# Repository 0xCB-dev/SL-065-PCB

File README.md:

# Synth Labs 065 PCB
## 65% Keyboard

Licence | OSHWA
:-------------------------:|:-------------------------:
 | TBD

### PCB:
KiCad version 6 stable

Top | Bottom
:-------------------------:|:-------------------------:
  |  

#### BOM:

[ibom pcb](https://files.0xcb.dev/0xCB/SL-065-PCB/pcb.html)

##### Hotswap PCB

| References                             | Value        | Footprint                                       | Quantity | Mouser                                                                                                              |
|----------------------------------------|--------------|-------------------------------------------------|----------|---------------------------------------------------------------------------------------------------------------------|

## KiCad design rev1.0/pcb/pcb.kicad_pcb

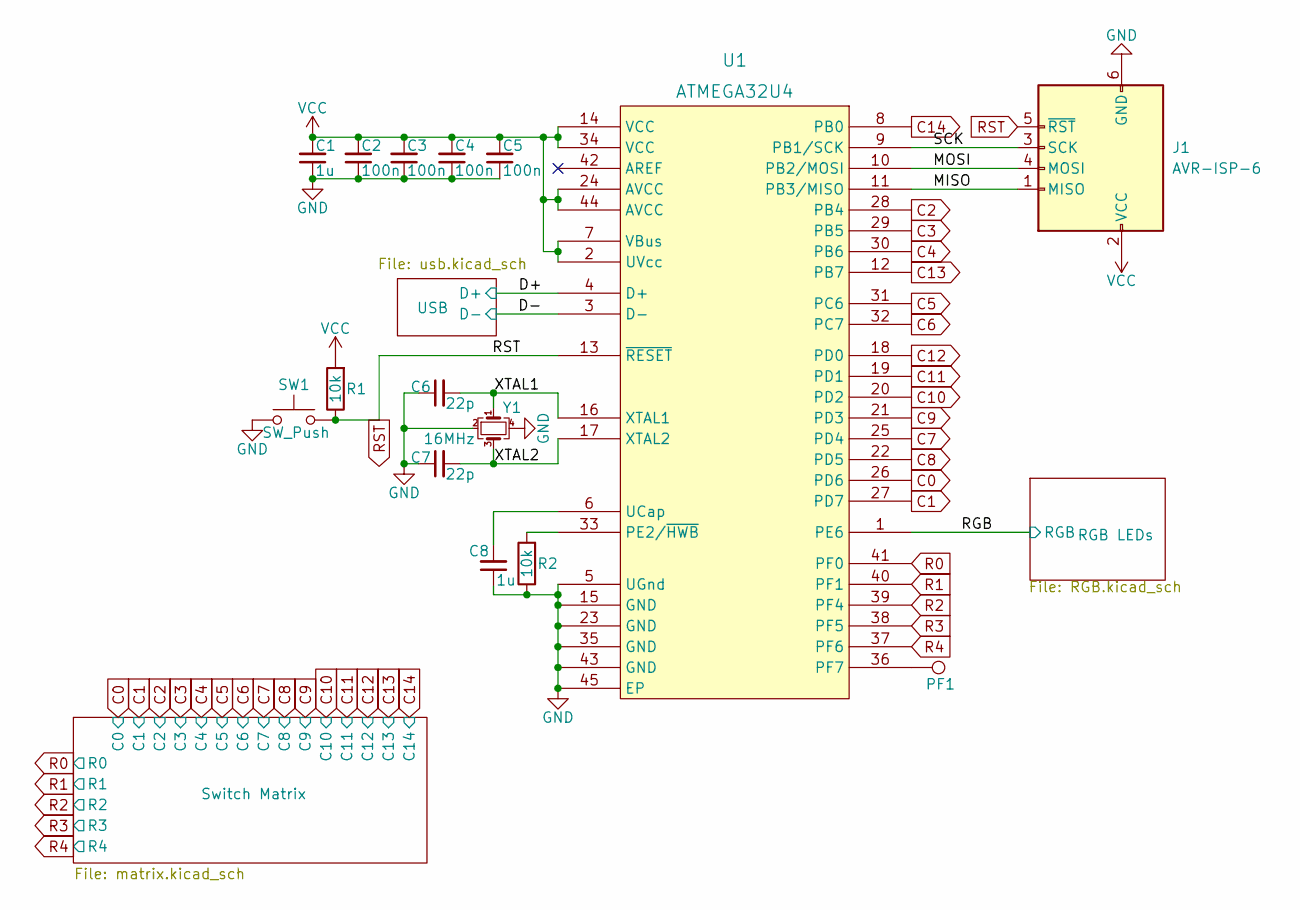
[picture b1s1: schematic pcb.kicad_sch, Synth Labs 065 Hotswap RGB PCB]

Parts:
C1, C8: 1u; C_0603_1608Metric
C2, C3, C4, C5: 100n; C_0603_1608Metric
C6, C7: 22p; C_0603_1608Metric
J1: AVR-ISP-6; AVR_PROG_2.54_THT
PF1: TestPoint; TestPoint_Pad_D1.5mm
R1, R2: 10k; R_0603_1608Metric
SW1: SW_Push; SW_SPST_TL3342
U1: ATMEGA32U4; QFN-44-1EP_7x7mm_P0.5mm_EP5.2x5.2mm_ThermalVias
Y1: 16MHz; Crystal_SMD_3225-4Pin_3.2x2.5mm

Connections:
/D+: U1.4 (D+); also elsewhere on the board
/D-: U1.3 (D-); also elsewhere on the board
/MISO: J1.1 (MISO), U1.11 (PB3/MISO)
/MOSI: J1.4 (MOSI), U1.10 (PB2/MOSI)
/RGB: U1.1 (PE6); also elsewhere on the board
/SCK: J1.3 (SCK), U1.9 (PB1/SCK)
/XTAL1: C6.2, U1.16 (XTAL1), Y1.1
/XTAL2: C7.2, U1.17 (XTAL2), Y1.3
C0: U1.26 (PD6); also elsewhere on the board
C1: U1.27 (PD7); also elsewhere on the board
C2: U1.28 (PB4); also elsewhere on the board
C3: U1.29 (PB5); also elsewhere on the board
C4: U1.30 (PB6); also elsewhere on the board
C5: U1.31 (PC6); also elsewhere on the board
C6: U1.32 (PC7); also elsewhere on the board
C7: U1.25 (PD4); also elsewhere on the board
C8: U1.22 (PD5); also elsewhere on the board
C9: U1.21 (PD3); also elsewhere on the board
C10: U1.20 (PD2); also elsewhere on the board
C11: U1.19 (PD1); also elsewhere on the board
C12: U1.18 (PD0); also elsewhere on the board
C13: U1.12 (PB7); also elsewhere on the board
C14: U1.8 (PB0); also elsewhere on the board
GND: C1.1, C2.1, C3.1, C4.1, C5.1, C6.1, C7.1, C8.1, J1.6 (GND), R2.1, SW1.1, U1.5 (UGnd), U1.15 (GND), U1.23 (GND), U1.35 (GND), U1.43 (GND), U1.45 (EP), Y1.2, Y1.4; also elsewhere on the board
unnamed: C8.2, U1.6 (UCap)
unnamed: PF1.1, U1.36 (PF7)
unnamed: R2.2, U1.33 (PE2/~HWB)
R0: U1.41 (PF0); also elsewhere on the board
R1: U1.40 (PF1); also elsewhere on the board
R2: U1.39 (PF4); also elsewhere on the board
R3: U1.38 (PF5); also elsewhere on the board
R4: U1.37 (PF6); also elsewhere on the board
RST: J1.5 (~RST), R1.1, SW1.2, U1.13 (~RESET)
VCC: C1.2, C2.2, C3.2, C4.2, C5.2, J1.2 (VCC), R1.2, U1.2 (UVcc), U1.7 (VBus), U1.14 (VCC), U1.24 (AVCC), U1.34 (VCC), U1.44 (AVCC); also elsewhere on the board

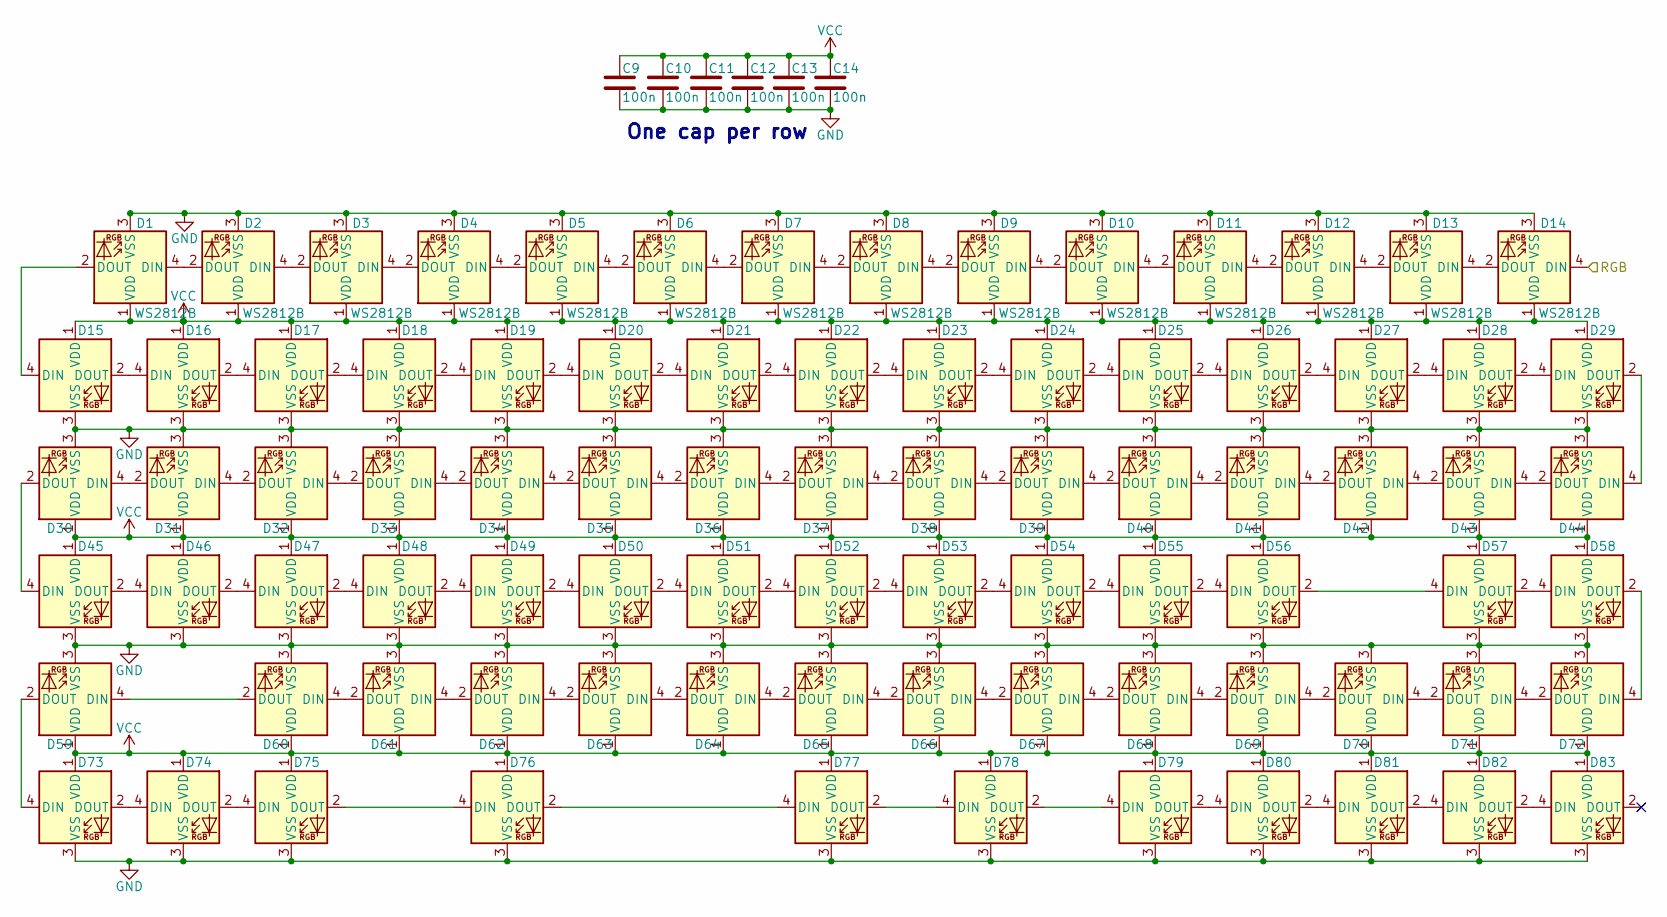
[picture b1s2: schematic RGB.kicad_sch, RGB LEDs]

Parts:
C9, C10, C11, C12, C13, C14: 100n; C_0603_1608Metric
D1, D2, D3, D4, D5, D6, D7, D8, D9, D10, D11, D12, D13, D14: WS2812B; LED_WS2812B_PLCC4_5.0x5.0mm_P3.2mm
D15, D16, D17, D18, D19, D20, D21, D22, D23, D24, D25, D26, D27, D28, D29, D30, D31, D32, D33, D34, D35, D36, D37, D38, D39, D40, D41, D42, D43, D44, D45, D46, D47, D48, D49, D50, D51, D52, D53, D54, D55, D56, D57, D58, D59, D60, D61, D62, D63, D64, D65, D66, D67, D68, D69, D70, D71, D72, D73, D74, D75, D76, D77, D78, D79, D80, D81, D82, D83: SK6812MINI-E; MX_SK6812MINI-E

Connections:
/RGB: D14.4 (DIN); also elsewhere on the board
GND: C9.2, C10.2, C11.2, C12.2, C13.2, C14.2, D1.3 (VSS), D2.3 (VSS), D3.3 (VSS), D4.3 (VSS), D5.3 (VSS), D6.3 (VSS), D7.3 (VSS), D8.3 (VSS), D9.3 (VSS), D10.3 (VSS), D11.3 (VSS), D12.3 (VSS), D13.3 (VSS), D14.3 (VSS), D15.3 (VSS), D16.3 (VSS), D17.3 (VSS), D18.3 (VSS), D19.3 (VSS), D20.3 (VSS), D21.3 (VSS), D22.3 (VSS), D23.3 (VSS), D24.3 (VSS), D25.3 (VSS), D26.3 (VSS), D27.3 (VSS), D28.3 (VSS), D29.3 (VSS), D30.3 (VSS), D31.3 (VSS), D32.3 (VSS), D33.3 (VSS), D34.3 (VSS), D35.3 (VSS), D36.3 (VSS), D37.3 (VSS), D38.3 (VSS), D39.3 (VSS), D40.3 (VSS), D41.3 (VSS), D42.3 (VSS), D43.3 (VSS), D44.3 (VSS), D45.3 (VSS), D46.3 (VSS), D47.3 (VSS), D48.3 (VSS), D49.3 (VSS), D50.3 (VSS), D51.3 (VSS), D52.3 (VSS), D53.3 (VSS), D54.3 (VSS), D55.3 (VSS), D56.3 (VSS), D57.3 (VSS), D58.3 (VSS), D59.3 (VSS), D60.3 (VSS), D61.3 (VSS), D62.3 (VSS), D63.3 (VSS), D64.3 (VSS), D65.3 (VSS), D66.3 (VSS), D67.3 (VSS), D68.3 (VSS), D69.3 (VSS), D70.3 (VSS), D71.3 (VSS), D72.3 (VSS), D73.3 (VSS), D74.3 (VSS), D75.3 (VSS), D76.3 (VSS), D77.3 (VSS), D78.3 (VSS), D79.3 (VSS), D80.3 (VSS), D81.3 (VSS), D82.3 (VSS), D83.3 (VSS); also elsewhere on the board
unnamed: D1.2 (DOUT), D15.4 (DIN)
unnamed: D1.4 (DIN), D2.2 (DOUT)
unnamed: D2.4 (DIN), D3.2 (DOUT)
unnamed: D3.4 (DIN), D4.2 (DOUT)
unnamed: D4.4 (DIN), D5.2 (DOUT)
unnamed: D5.4 (DIN), D6.2 (DOUT)
unnamed: D6.4 (DIN), D7.2 (DOUT)
unnamed: D7.4 (DIN), D8.2 (DOUT)
unnamed: D8.4 (DIN), D9.2 (DOUT)
unnamed: D9.4 (DIN), D10.2 (DOUT)
unnamed: D10.4 (DIN), D11.2 (DOUT)
unnamed: D11.4 (DIN), D12.2 (DOUT)
unnamed: D12.4 (DIN), D13.2 (DOUT)
unnamed: D13.4 (DIN), D14.2 (DOUT)
unnamed: D15.2 (DOUT), D16.4 (DIN)
unnamed: D16.2 (DOUT), D17.4 (DIN)
unnamed: D17.2 (DOUT), D18.4 (DIN)
unnamed: D18.2 (DOUT), D19.4 (DIN)
unnamed: D19.2 (DOUT), D20.4 (DIN)
unnamed: D20.2 (DOUT), D21.4 (DIN)
unnamed: D21.2 (DOUT), D22.4 (DIN)
unnamed: D22.2 (DOUT), D23.4 (DIN)
unnamed: D23.2 (DOUT), D24.4 (DIN)
unnamed: D24.2 (DOUT), D25.4 (DIN)
unnamed: D25.2 (DOUT), D26.4 (DIN)
unnamed: D26.2 (DOUT), D27.4 (DIN)
unnamed: D27.2 (DOUT), D28.4 (DIN)
unnamed: D28.2 (DOUT), D29.4 (DIN)
unnamed: D29.2 (DOUT), D44.4 (DIN)
unnamed: D30.2 (DOUT), D45.4 (DIN)
unnamed: D30.4 (DIN), D31.2 (DOUT)
unnamed: D31.4 (DIN), D32.2 (DOUT)
unnamed: D32.4 (DIN), D33.2 (DOUT)
unnamed: D33.4 (DIN), D34.2 (DOUT)
unnamed: D34.4 (DIN), D35.2 (DOUT)
unnamed: D35.4 (DIN), D36.2 (DOUT)
unnamed: D36.4 (DIN), D37.2 (DOUT)
unnamed: D37.4 (DIN), D38.2 (DOUT)
unnamed: D38.4 (DIN), D39.2 (DOUT)
unnamed: D39.4 (DIN), D40.2 (DOUT)
unnamed: D40.4 (DIN), D41.2 (DOUT)
unnamed: D41.4 (DIN), D42.2 (DOUT)
unnamed: D42.4 (DIN), D43.2 (DOUT)
unnamed: D43.4 (DIN), D44.2 (DOUT)
unnamed: D45.2 (DOUT), D46.4 (DIN)
unnamed: D46.2 (DOUT), D47.4 (DIN)
unnamed: D47.2 (DOUT), D48.4 (DIN)
unnamed: D48.2 (DOUT), D49.4 (DIN)
unnamed: D49.2 (DOUT), D50.4 (DIN)
unnamed: D50.2 (DOUT), D51.4 (DIN)
unnamed: D51.2 (DOUT), D52.4 (DIN)
unnamed: D52.2 (DOUT), D53.4 (DIN)
unnamed: D53.2 (DOUT), D54.4 (DIN)
unnamed: D54.2 (DOUT), D55.4 (DIN)
unnamed: D55.2 (DOUT), D56.4 (DIN)
unnamed: D56.2 (DOUT), D57.4 (DIN)
unnamed: D57.2 (DOUT), D58.4 (DIN)
unnamed: D58.2 (DOUT), D72.4 (DIN)
unnamed: D59.2 (DOUT), D73.4 (DIN)
unnamed: D59.4 (DIN), D60.2 (DOUT)
unnamed: D60.4 (DIN), D61.2 (DOUT)
unnamed: D61.4 (DIN), D62.2 (DOUT)
unnamed: D62.4 (DIN), D63.2 (DOUT)
unnamed: D63.4 (DIN), D64.2 (DOUT)
unnamed: D64.4 (DIN), D65.2 (DOUT)
unnamed: D65.4 (DIN), D66.2 (DOUT)
unnamed: D66.4 (DIN), D67.2 (DOUT)
unnamed: D67.4 (DIN), D68.2 (DOUT)
unnamed: D68.4 (DIN), D69.2 (DOUT)
unnamed: D69.4 (DIN), D70.2 (DOUT)
unnamed: D70.4 (DIN), D71.2 (DOUT)
unnamed: D71.4 (DIN), D72.2 (DOUT)
unnamed: D73.2 (DOUT), D74.4 (DIN)
unnamed: D74.2 (DOUT), D75.4 (DIN)
unnamed: D75.2 (DOUT), D76.4 (DIN)
unnamed: D76.2 (DOUT), D77.4 (DIN)
unnamed: D77.2 (DOUT), D78.4 (DIN)
unnamed: D78.2 (DOUT), D79.4 (DIN)
unnamed: D79.2 (DOUT), D80.4 (DIN)
unnamed: D80.2 (DOUT), D81.4 (DIN)
unnamed: D81.2 (DOUT), D82.4 (DIN)
unnamed: D82.2 (DOUT), D83.4 (DIN)
VCC: C9.1, C10.1, C11.1, C12.1, C13.1, C14.1, D1.1 (VDD), D2.1 (VDD), D3.1 (VDD), D4.1 (VDD), D5.1 (VDD), D6.1 (VDD), D7.1 (VDD), D8.1 (VDD), D9.1 (VDD), D10.1 (VDD), D11.1 (VDD), D12.1 (VDD), D13.1 (VDD), D14.1 (VDD), D15.1 (VDD), D16.1 (VDD), D17.1 (VDD), D18.1 (VDD), D19.1 (VDD), D20.1 (VDD), D21.1 (VDD), D22.1 (VDD), D23.1 (VDD), D24.1 (VDD), D25.1 (VDD), D26.1 (VDD), D27.1 (VDD), D28.1 (VDD), D29.1 (VDD), D30.1 (VDD), D31.1 (VDD), D32.1 (VDD), D33.1 (VDD), D34.1 (VDD), D35.1 (VDD), D36.1 (VDD), D37.1 (VDD), D38.1 (VDD), D39.1 (VDD), D40.1 (VDD), D41.1 (VDD), D42.1 (VDD), D43.1 (VDD), D44.1 (VDD), D45.1 (VDD), D46.1 (VDD), D47.1 (VDD), D48.1 (VDD), D49.1 (VDD), D50.1 (VDD), D51.1 (VDD), D52.1 (VDD), D53.1 (VDD), D54.1 (VDD), D55.1 (VDD), D56.1 (VDD), D57.1 (VDD), D58.1 (VDD), D59.1 (VDD), D60.1 (VDD), D61.1 (VDD), D62.1 (VDD), D63.1 (VDD), D64.1 (VDD), D65.1 (VDD), D66.1 (VDD), D67.1 (VDD), D68.1 (VDD), D69.1 (VDD), D70.1 (VDD), D71.1 (VDD), D72.1 (VDD), D73.1 (VDD), D74.1 (VDD), D75.1 (VDD), D76.1 (VDD), D77.1 (VDD), D78.1 (VDD), D79.1 (VDD), D80.1 (VDD), D81.1 (VDD), D82.1 (VDD), D83.1 (VDD); also elsewhere on the board

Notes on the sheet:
One cap per row

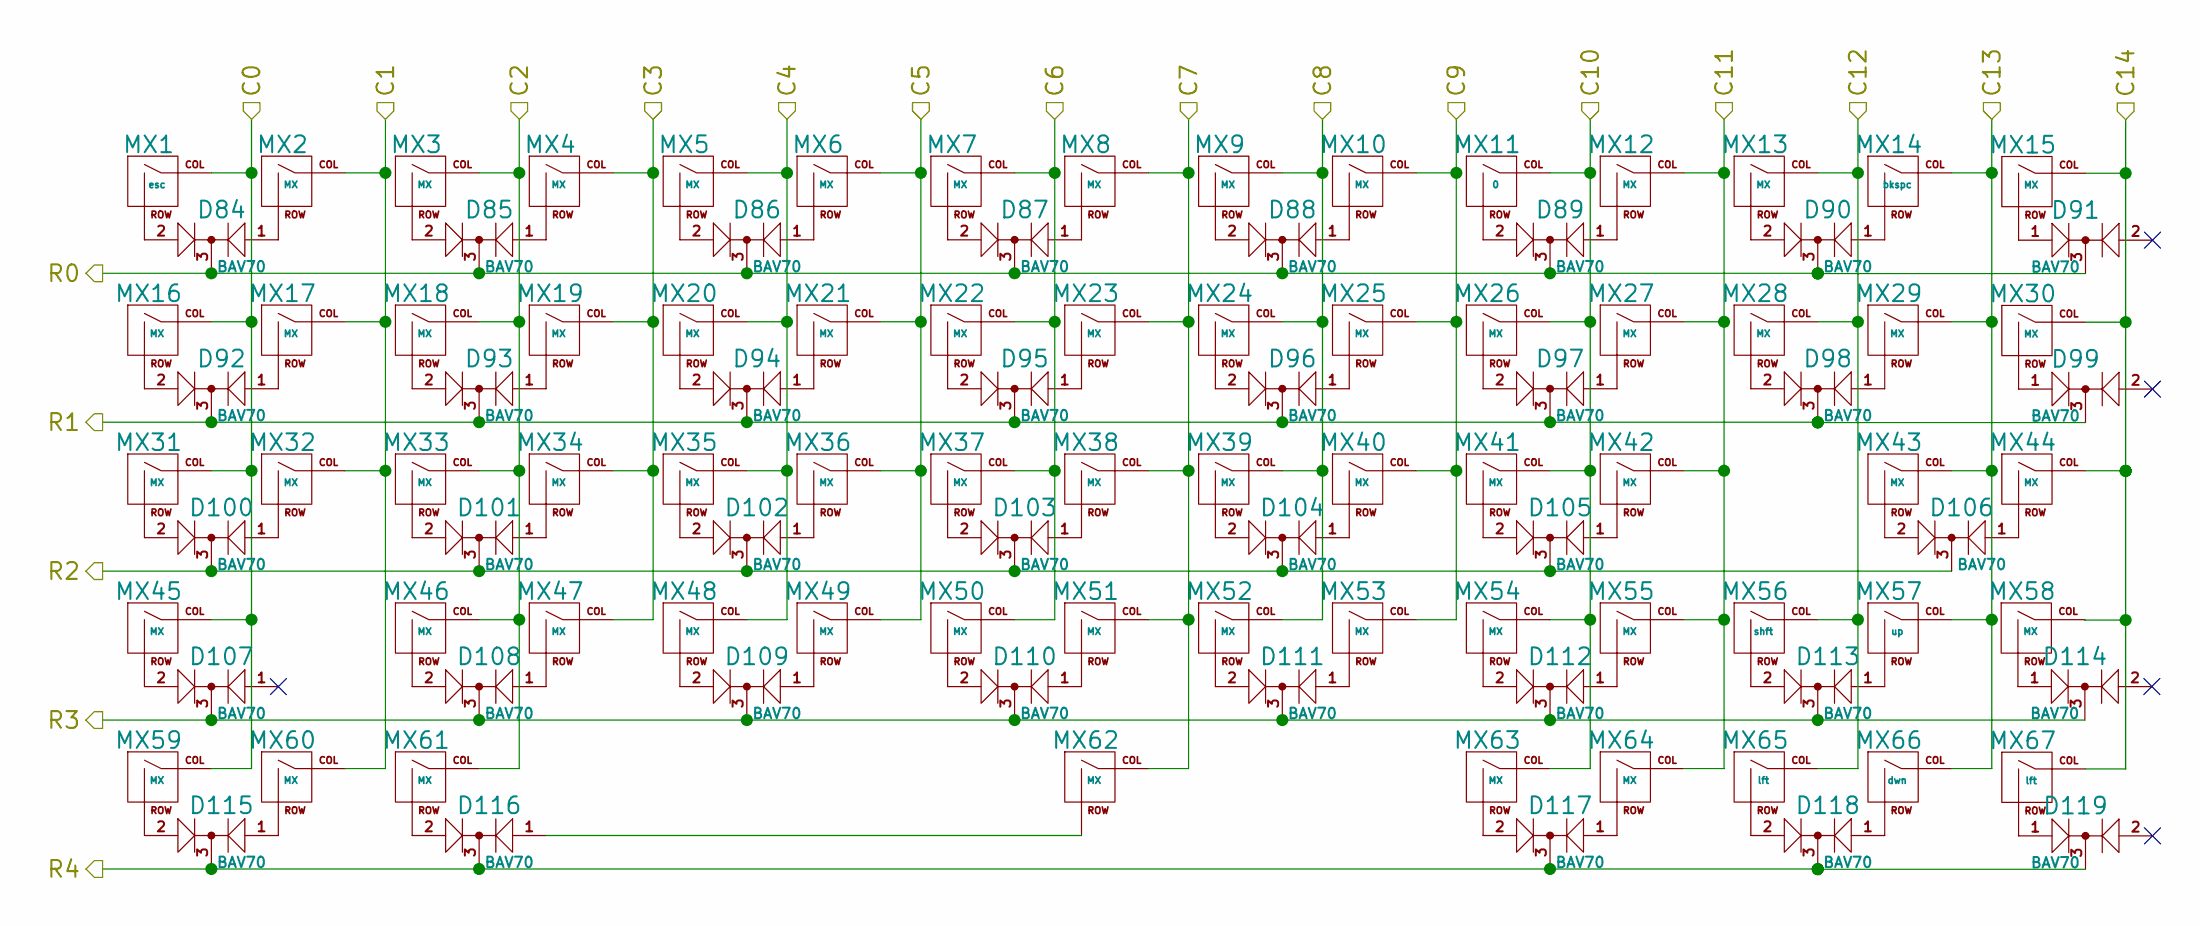
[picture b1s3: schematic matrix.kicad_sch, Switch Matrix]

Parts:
D84, D85, D86, D87, D88, D89, D90, D91, D92, D93, D94, D95, D96, D97, D98, D99, D100, D101, D102, D103, D104, D105, D106, D107, D108, D109, D110, D111, D112, D113, D114, D115, D116, D117, D118, D119: BAV70; SOT-23
MX1: esc; SW_Hotswap_Kailh_1.00u
MX2, MX3, MX4, MX5, MX6, MX7, MX8, MX9, MX10, MX12, MX13, MX15, MX17, MX18, MX19, MX20, MX21, MX22, MX23, MX24, MX25, MX26, MX27, MX28, MX30, MX32, MX33, MX34, MX35, MX36, MX37, MX38, MX39, MX40, MX41, MX42, MX44, MX46, MX47, MX48, MX49, MX50, MX51, MX52, MX53, MX54, MX55, MX58: MX; SW_Hotswap_Kailh_1.00u
MX11: 0; SW_Hotswap_Kailh_1.00u
MX14: bkspc; SW_Hotswap_Kailh_2.00u
MX16, MX29: MX; SW_Hotswap_Kailh_1.50u
MX31: MX; SW_Hotswap_Kailh_1.75u
MX43, MX45: MX; SW_Hotswap_Kailh_2.25u
MX56: shft; SW_Hotswap_Kailh_1.75u
MX57: up; SW_Hotswap_Kailh_1.00u
MX59, MX60, MX61, MX63, MX64: MX; SW_Hotswap_Kailh_1.25u
MX62: MX; SW_Hotswap_Kailh_6.25u
MX65, MX67: lft; SW_Hotswap_Kailh_1.00u
MX66: dwn; SW_Hotswap_Kailh_1.00u

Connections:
C0: MX1.1 (COL), MX16.1 (COL), MX31.1 (COL), MX45.1 (COL), MX59.1 (COL); also elsewhere on the board
C1: MX2.1 (COL), MX17.1 (COL), MX32.1 (COL), MX60.1 (COL); also elsewhere on the board
C2: MX3.1 (COL), MX18.1 (COL), MX33.1 (COL), MX46.1 (COL), MX61.1 (COL); also elsewhere on the board
C3: MX4.1 (COL), MX19.1 (COL), MX34.1 (COL), MX47.1 (COL); also elsewhere on the board
C4: MX5.1 (COL), MX20.1 (COL), MX35.1 (COL), MX48.1 (COL); also elsewhere on the board
C5: MX6.1 (COL), MX21.1 (COL), MX36.1 (COL), MX49.1 (COL); also elsewhere on the board
C6: MX7.1 (COL), MX22.1 (COL), MX37.1 (COL), MX50.1 (COL); also elsewhere on the board
C7: MX8.1 (COL), MX23.1 (COL), MX38.1 (COL), MX51.1 (COL), MX62.1 (COL); also elsewhere on the board
C8: MX9.1 (COL), MX24.1 (COL), MX39.1 (COL), MX52.1 (COL); also elsewhere on the board
C9: MX10.1 (COL), MX25.1 (COL), MX40.1 (COL), MX53.1 (COL); also elsewhere on the board
C10: MX11.1 (COL), MX26.1 (COL), MX41.1 (COL), MX54.1 (COL), MX63.1 (COL); also elsewhere on the board
C11: MX12.1 (COL), MX27.1 (COL), MX42.1 (COL), MX55.1 (COL), MX64.1 (COL); also elsewhere on the board
C12: MX13.1 (COL), MX28.1 (COL), MX56.1 (COL), MX65.1 (COL); also elsewhere on the board
C13: MX14.1 (COL), MX29.1 (COL), MX43.1 (COL), MX57.1 (COL), MX66.1 (COL); also elsewhere on the board
C14: MX15.1 (COL), MX30.1 (COL), MX44.1 (COL), MX58.1 (COL), MX67.1 (COL); also elsewhere on the board
unnamed: D84.1 (A1), MX2.2 (ROW)
unnamed: D84.2 (A2), MX1.2 (ROW)
unnamed: D85.1 (A1), MX4.2 (ROW)
unnamed: D85.2 (A2), MX3.2 (ROW)
unnamed: D86.1 (A1), MX6.2 (ROW)
unnamed: D86.2 (A2), MX5.2 (ROW)
unnamed: D87.1 (A1), MX8.2 (ROW)
unnamed: D87.2 (A2), MX7.2 (ROW)
unnamed: D88.1 (A1), MX10.2 (ROW)
unnamed: D88.2 (A2), MX9.2 (ROW)
unnamed: D89.1 (A1), MX12.2 (ROW)
unnamed: D89.2 (A2), MX11.2 (ROW)
unnamed: D90.1 (A1), MX14.2 (ROW)
unnamed: D90.2 (A2), MX13.2 (ROW)
unnamed: D91.1 (A1), MX15.2 (ROW)
unnamed: D92.1 (A1), MX17.2 (ROW)
unnamed: D92.2 (A2), MX16.2 (ROW)
unnamed: D93.1 (A1), MX19.2 (ROW)
unnamed: D93.2 (A2), MX18.2 (ROW)
unnamed: D94.1 (A1), MX21.2 (ROW)
unnamed: D94.2 (A2), MX20.2 (ROW)
unnamed: D95.1 (A1), MX23.2 (ROW)
unnamed: D95.2 (A2), MX22.2 (ROW)
unnamed: D96.1 (A1), MX25.2 (ROW)
unnamed: D96.2 (A2), MX24.2 (ROW)
unnamed: D97.1 (A1), MX27.2 (ROW)
unnamed: D97.2 (A2), MX26.2 (ROW)
unnamed: D98.1 (A1), MX29.2 (ROW)
unnamed: D98.2 (A2), MX28.2 (ROW)
unnamed: D99.1 (A1), MX30.2 (ROW)
unnamed: D100.1 (A1), MX32.2 (ROW)
unnamed: D100.2 (A2), MX31.2 (ROW)
unnamed: D101.1 (A1), MX34.2 (ROW)
unnamed: D101.2 (A2), MX33.2 (ROW)
unnamed: D102.1 (A1), MX36.2 (ROW)
unnamed: D102.2 (A2), MX35.2 (ROW)
unnamed: D103.1 (A1), MX38.2 (ROW)
unnamed: D103.2 (A2), MX37.2 (ROW)
unnamed: D104.1 (A1), MX40.2 (ROW)
unnamed: D104.2 (A2), MX39.2 (ROW)
unnamed: D105.1 (A1), MX42.2 (ROW)
unnamed: D105.2 (A2), MX41.2 (ROW)
unnamed: D106.1 (A1), MX44.2 (ROW)
unnamed: D106.2 (A2), MX43.2 (ROW)
unnamed: D107.2 (A2), MX45.2 (ROW)
unnamed: D108.1 (A1), MX47.2 (ROW)
unnamed: D108.2 (A2), MX46.2 (ROW)
unnamed: D109.1 (A1), MX49.2 (ROW)
unnamed: D109.2 (A2), MX48.2 (ROW)
unnamed: D110.1 (A1), MX51.2 (ROW)
unnamed: D110.2 (A2), MX50.2 (ROW)
unnamed: D111.1 (A1), MX53.2 (ROW)
unnamed: D111.2 (A2), MX52.2 (ROW)
unnamed: D112.1 (A1), MX55.2 (ROW)
unnamed: D112.2 (A2), MX54.2 (ROW)
unnamed: D113.1 (A1), MX57.2 (ROW)
unnamed: D113.2 (A2), MX56.2 (ROW)
unnamed: D114.1 (A1), MX58.2 (ROW)
unnamed: D115.1 (A1), MX60.2 (ROW)
unnamed: D115.2 (A2), MX59.2 (ROW)
unnamed: D116.1 (A1), MX62.2 (ROW)
unnamed: D116.2 (A2), MX61.2 (ROW)
unnamed: D117.1 (A1), MX64.2 (ROW)
unnamed: D117.2 (A2), MX63.2 (ROW)
unnamed: D118.1 (A1), MX66.2 (ROW)
unnamed: D118.2 (A2), MX65.2 (ROW)
unnamed: D119.1 (A1), MX67.2 (ROW)
R0: D84.3 (K), D85.3 (K), D86.3 (K), D87.3 (K), D88.3 (K), D89.3 (K), D90.3 (K), D91.3 (K); also elsewhere on the board
R1: D92.3 (K), D93.3 (K), D94.3 (K), D95.3 (K), D96.3 (K), D97.3 (K), D98.3 (K), D99.3 (K); also elsewhere on the board
R2: D100.3 (K), D101.3 (K), D102.3 (K), D103.3 (K), D104.3 (K), D105.3 (K), D106.3 (K); also elsewhere on the board
R3: D107.3 (K), D108.3 (K), D109.3 (K), D110.3 (K), D111.3 (K), D112.3 (K), D113.3 (K), D114.3 (K); also elsewhere on the board
R4: D115.3 (K), D116.3 (K), D117.3 (K), D118.3 (K), D119.3 (K); also elsewhere on the board

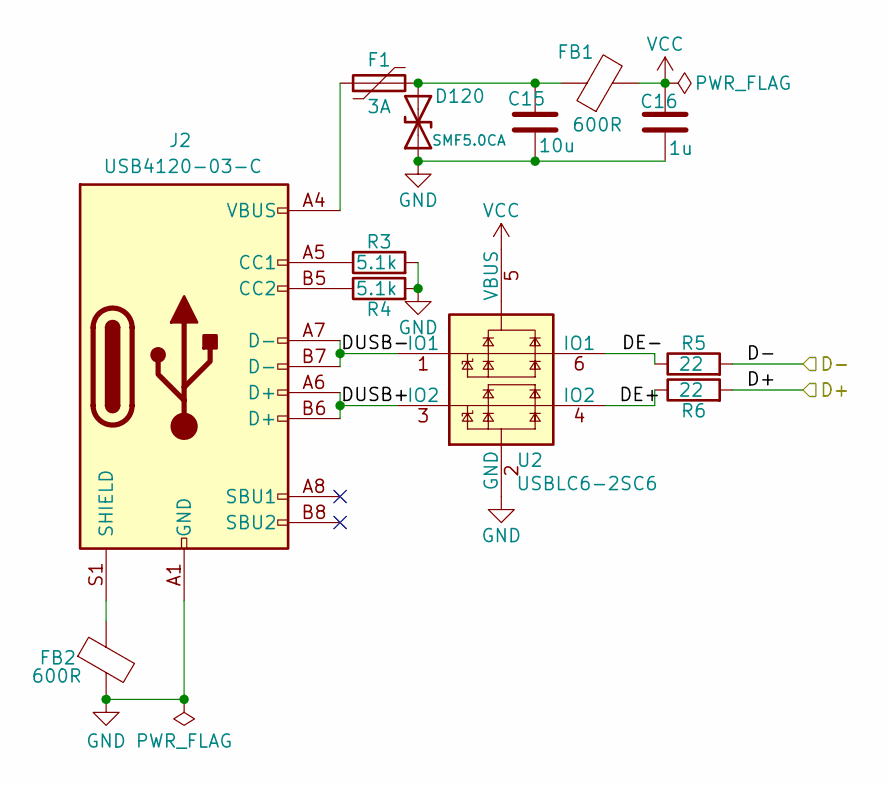
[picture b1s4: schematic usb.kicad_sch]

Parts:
C15: 10u; C_0603_1608Metric
C16: 1u; C_0603_1608Metric
D120: SMF5.0CA; D_SOD-123F
F1: 3A; Fuse_0805_2012Metric
FB1, FB2: 600R; Ferrite_Bead_0603
J2: USB4120-03-C; GCT_USB4105_REVA
R3, R4: 5.1k; R_0603_1608Metric
R5, R6: 22; R_0603_1608Metric
U2: USBLC6-2SC6; SOT-23-6

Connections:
/D+: R6.2; also elsewhere on the board
/D-: R5.2; also elsewhere on the board
/USB/DE+: R6.1, U2.4 (IO2)
/USB/DE-: R5.1, U2.6 (IO1)
/USB/DUSB+: J2.A6 (D+), J2.B6 (D+), U2.3 (IO2)
/USB/DUSB-: J2.A7 (D-), J2.B7 (D-), U2.1 (IO1)
GND: C15.2, C16.2, D120.1 (A1), FB2.2, J2.A1 (GND), J2.A12 (GND), J2.B1 (GND), J2.B12 (GND), R3.2, R4.2, U2.2 (GND); also elsewhere on the board
unnamed: C15.1, D120.2 (A2), F1.2, FB1.1
unnamed: F1.1, J2.A4 (VBUS), J2.A9 (VBUS), J2.B4 (VBUS), J2.B9 (VBUS)
unnamed: FB2.1, J2.S1 (SHIELD)
unnamed: J2.A5 (CC1), R3.1
unnamed: J2.B5 (CC2), R4.1
VCC: C16.1, FB1.2, U2.5 (VBUS); also elsewhere on the board

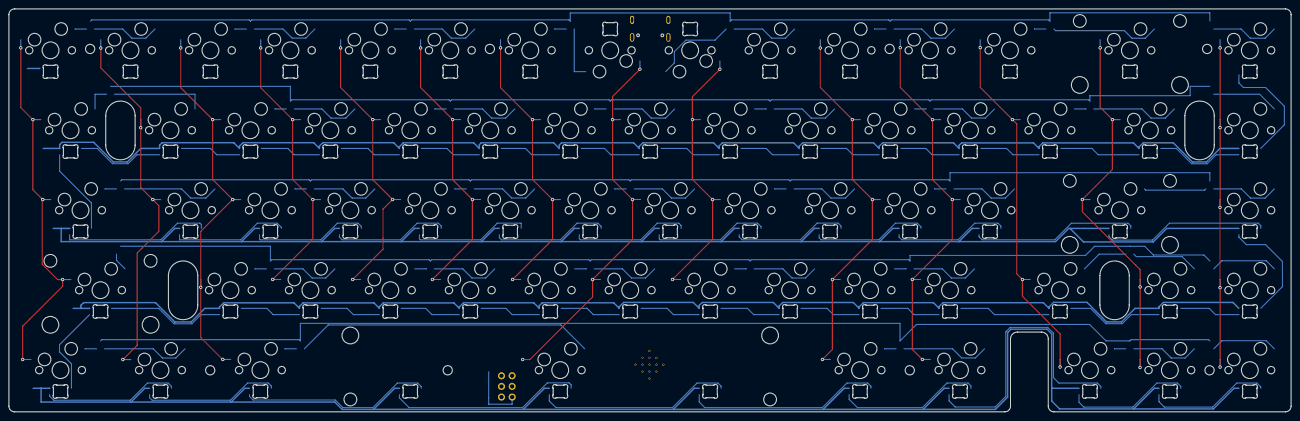
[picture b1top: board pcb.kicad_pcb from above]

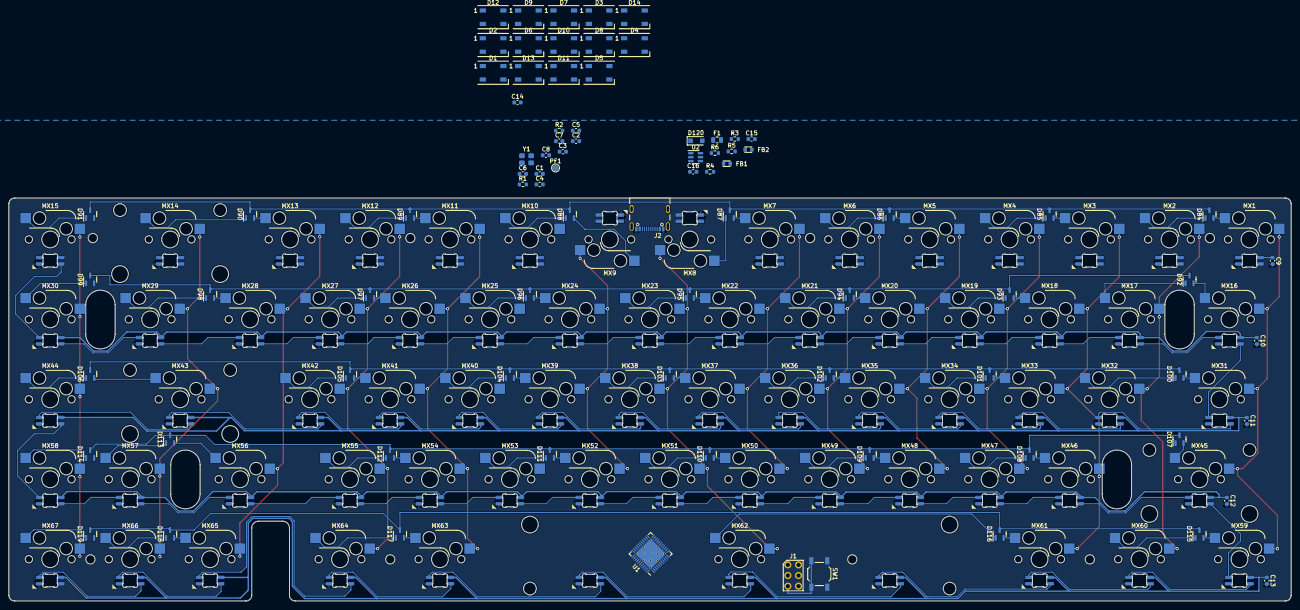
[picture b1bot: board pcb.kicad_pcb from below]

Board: 2 copper layers, 305.5 x 96.0 mm, 219 parts (83 on the bottom side), 192 nets.

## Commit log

2021-11-01 schematic done
2021-11-02 pcb layout done
2021-11-03 Columns and Rows
2021-11-03 edited schematic and fixed constraints
2021-11-03 Did the rows... again
2021-11-04 RGB LED Stuff
2021-11-05 Worked on USB Stuff
2021-11-06 Did some columns and rows to controller
2021-11-06 Changed position of Controller
2021-11-08 addes HS LEDs
2021-11-08 Placed mini LEDs
2021-11-21 colums, rows and RGB done
2021-11-22 fixed vcc and other issues
2021-11-23 VCC fixed and done
2021-11-23 fixed ground plane
2021-11-29 ckecked pcb
2021-12-02 updated outline and screw hole locations
2021-12-03 worked on rounded traces
2021-12-04 frontside rounding finished
2021-12-05 rounding done
2021-12-07 added some ground vias
2021-12-19 removed silkscreen
2022-01-08 added gitignore
2022-01-08 added 2D renders
2022-01-16 changed placement of backspace LEDs
2022-01-17 changed ISP from Through Hole to Pad
2022-09-06 forgot rounded track
2023-01-02 Adjust board outline
2023-01-11 fix bootom row rgb routing
2023-03-19 rp2040 port: updated schematic and fixed footprints
2023-04-10 routing of RP2040
2023-04-11 fixed DRC, added thermal vias, fixed usb GND and TLT
2023-04-12 first side rounded
2023-04-18 finished rounding
2023-04-22 removed some more silkscreen, rounded data lines
2023-04-25 fixup and add prod
2023-04-25 Update kikit-commands.txt
    typo
2023-05-11 Adjust standoff hole outline
2023-05-11 Repanelize and regenerate production gerbers
2023-05-16 Add soldered PCB. Rename original PCB to hotswap PCB.
